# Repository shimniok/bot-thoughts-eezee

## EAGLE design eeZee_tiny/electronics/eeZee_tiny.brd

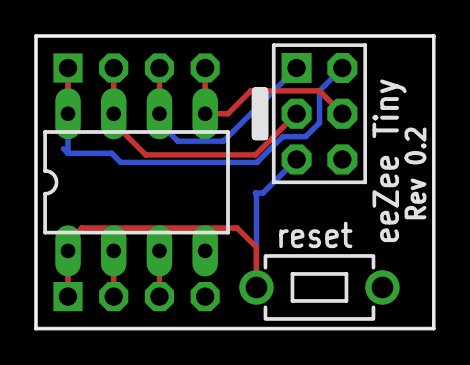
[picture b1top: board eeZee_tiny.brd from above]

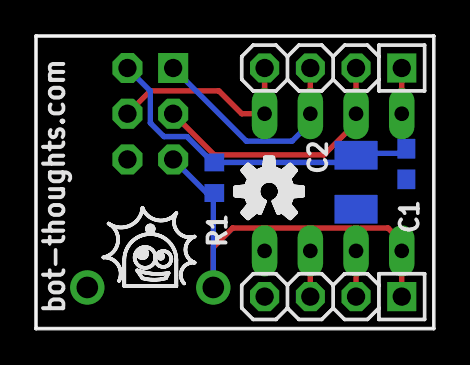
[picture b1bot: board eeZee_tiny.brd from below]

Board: 2 copper layers, 22.1 x 16.3 mm, 8 parts (5 on the bottom side), 8 nets.

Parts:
C1: 0.1uF; C0603
C2: 100uF; SMC_B
IC1: attiny; DIL08
J2: avrisp; CON6P2R
JP3, JP4: 1X04-S
R1: 10k; R0603
S1: reset; 6MMTACTILE_RECT

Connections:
!RESET: IC1.1, J2.5, JP3.1, R1.1, S1.P$1
GND: C1.2, C2.-, IC1.4, J2.6, JP3.4, S1.P$2
MISO: IC1.6, J2.1, JP4.3
MOSI: IC1.5, J2.4, JP4.4
unnamed: IC1.2, JP3.2
unnamed: IC1.3, JP3.3
SCK: IC1.7, J2.3, JP4.2
VCC: C1.1, C2.+, IC1.8, J2.2, JP4.1, R1.2

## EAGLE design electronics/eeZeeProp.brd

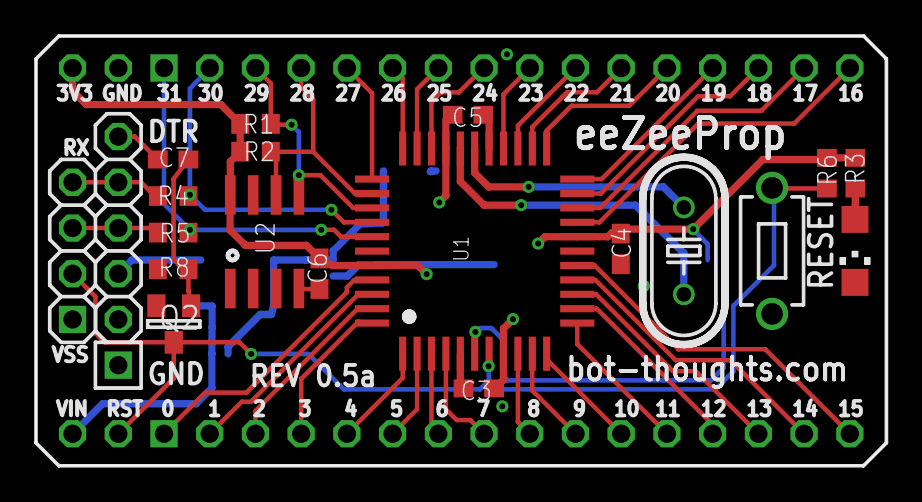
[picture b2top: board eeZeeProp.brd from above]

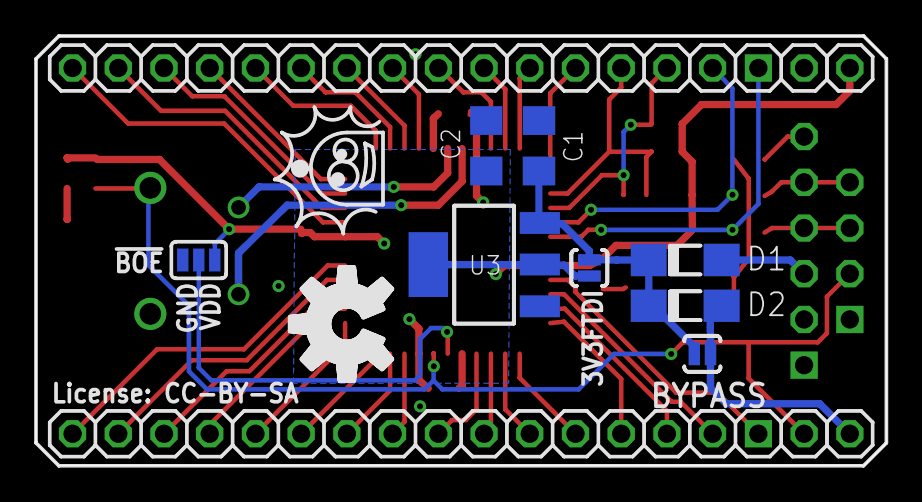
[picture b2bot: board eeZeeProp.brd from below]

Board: 2 copper layers, 47.2 x 23.9 mm, 34 parts (14 on the bottom side), 46 nets.

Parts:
C1, C2: 10uF; C1206
C3, C4, C5, C6, C7: 0.1uF; C0603
D1, D2: MBR130LSFT1; SOD123FL
JP1, JP5: 1X16-S
JP2: VIN; 1X01
JP3: PROP PLUG; 1X04-S
JP4: FTDI; 1X06-S
JP6: GND; 1X01
JP7: !RES; 1X01
JP8: 3V3; 1X01
LED1: green; CHIPLED_1206
Q1: 5MHz; HC49U-V
Q2: 2N3904SOT23; SOT-23
R1, R2, R4, R5, R8: 10k; R0603
R3: 330; R0603
R6: 1k; R0603
SJ1: BYPASS; SJ_2S-NO
SJ2: !BOE; SJ_3
SJ3: 3V3FTDI; SJ_2S-NO
SW1: RESET; 6MMTACTILE_RECT
U1: P8X32A-Q44
U2: 24LC256-I/ST; SO-08
U3: NCP1117 3V3; SOT223

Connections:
!BOE: SJ2.2, U1.6
!RES: JP3.2, JP7.1, Q2.1, R6.2, SW1.P$1, U1.7
DTR: C7.2, JP4.6
GND: C1.2, C2.2, C3.2, C4.2, C5.2, C6.2, JP3.1, JP4.1, JP6.1, LED1.C, Q2.2, R8.1, SJ2.1, SW1.P$2, U1.5, U1.17, U1.27, U1.39, U2.1, U2.2, U2.3, U2.4, U2.7, U3.1
unnamed: JP5.1, U1.41
unnamed: JP5.2, U1.42
unnamed: JP5.3, U1.43
unnamed: JP5.4, U1.44
unnamed: LED1.A, R3.1
unnamed: JP5.5, U1.1
unnamed: JP5.6, U1.2
unnamed: JP5.7, U1.3
unnamed: JP5.8, U1.4
unnamed: JP5.9, U1.9
unnamed: JP5.10, U1.10
unnamed: JP5.11, U1.11
unnamed: JP5.12, U1.12
unnamed: JP5.13, U1.13
unnamed: JP5.14, U1.14
unnamed: JP5.15, U1.15
unnamed: JP5.16, U1.16
unnamed: JP1.5, U1.34
unnamed: JP1.6, U1.33
unnamed: JP1.7, U1.32
unnamed: JP1.8, U1.31
unnamed: JP1.9, U1.26
unnamed: JP1.10, U1.25
unnamed: JP1.11, U1.24
unnamed: JP1.12, U1.23
unnamed: JP1.13, U1.22
unnamed: JP1.14, U1.21
unnamed: JP1.15, U1.20
unnamed: JP1.16, U1.19
unnamed: C7.1, Q2.3, R8.2
P28: JP1.4, R2.1, U1.35, U2.6
P29: JP1.3, R1.1, U1.36, U2.5
P30: JP1.2, R4.2, U1.37
P31: JP1.1, R5.2, U1.38
RXI: JP3.4, JP4.5, R4.1
TXO: JP3.3, JP4.4, R5.1
V+: C1.1, D1.C, D2.C, SJ1.2, SJ3.2, U3.3
VDD: C2.1, C3.1, C4.1, C5.1, C6.1, JP8.1, R1.2, R2.2, R3.2, R6.1, SJ2.3, SJ3.1, U1.8, U1.18, U1.30, U1.40, U2.8, U3.2, U3.4
VIN: D2.A, JP2.1, SJ1.1
VUSB: D1.A, JP4.3
XI: Q1.2, U1.28
XO: Q1.1, U1.29

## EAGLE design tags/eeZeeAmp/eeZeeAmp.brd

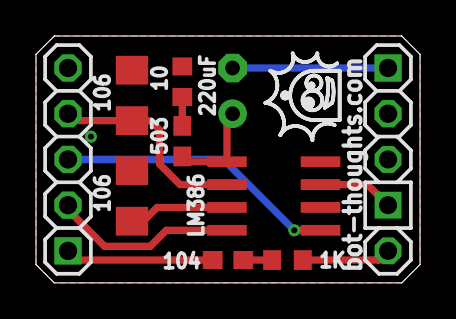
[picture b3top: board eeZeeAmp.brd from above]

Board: 2 copper layers, 21.3 x 13.7 mm, 11 parts (1 on the bottom side), 12 nets.

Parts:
C1: 220uF; E2,5-6
C2: 104; C0603
C3: 503; C0603
C4, C5: 106; C1206
IC1: LM386; SO08
JP1: 1X05-S
JP2: SPKR; 1X02-S
R1: 10; R0603
R2: VOL; OFFBOARD_POT_3
R3: 1K; R0603

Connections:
AUDIO: C2.1, JP1.1
G1: IC1.1, JP1.3
G8: IC1.8, JP1.2
GND: C4.2, C5.2, IC1.2, IC1.4, JP1.5, JP2.2, R1.1, R2.P$1
unnamed: IC1.3, R2.P$2
unnamed: C2.2, R3.2
unnamed: C1.+, C3.1, IC1.5
unnamed: C3.2, R1.2
unnamed: C5.1, IC1.7
unnamed: R2.P$3, R3.1
SP+: C1.-, JP2.1
VCC: C4.1, IC1.6, JP1.4

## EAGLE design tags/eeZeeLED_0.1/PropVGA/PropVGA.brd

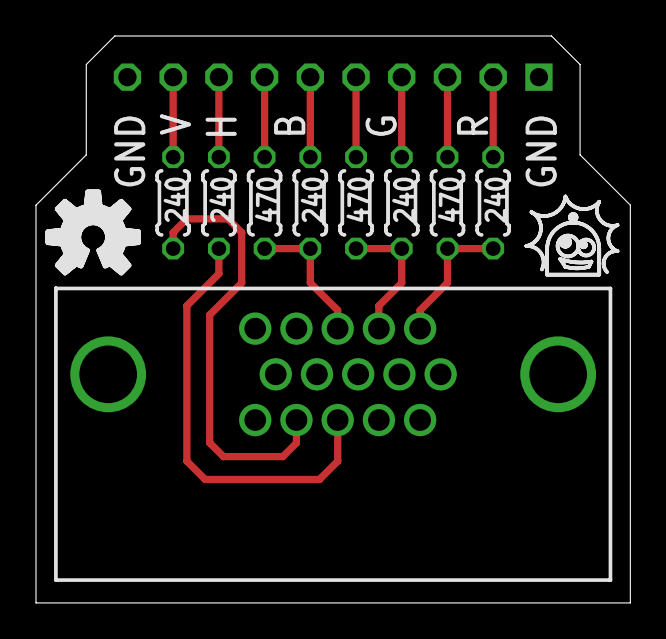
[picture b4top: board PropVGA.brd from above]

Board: 2 copper layers, 33.0 x 31.5 mm, 10 parts (1 on the bottom side), 14 nets.

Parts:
JP2: VGA; FCI_DSUB_HD_15_RA
JP3: 1X10-S
R1, R2, R4, R6, R8: 240; 0204/5
R3, R5, R7: 470; 0204/5

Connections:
B: JP2.P3, R3.1, R4.1
G: JP2.P2, R5.1, R6.1
GND: JP2.P5, JP2.P6, JP2.P7, JP2.P8, JP2.P9, JP2.P10, JP3.1, JP3.10
H: JP2.P13, R2.1
unnamed: JP3.9, R1.2
unnamed: JP3.8, R2.2
unnamed: JP3.7, R3.2
unnamed: JP3.6, R4.2
unnamed: JP3.5, R5.2
unnamed: JP3.4, R6.2
unnamed: JP3.3, R7.2
unnamed: JP3.2, R8.2
R: JP2.P1, R7.1, R8.1
V: JP2.P14, R1.1

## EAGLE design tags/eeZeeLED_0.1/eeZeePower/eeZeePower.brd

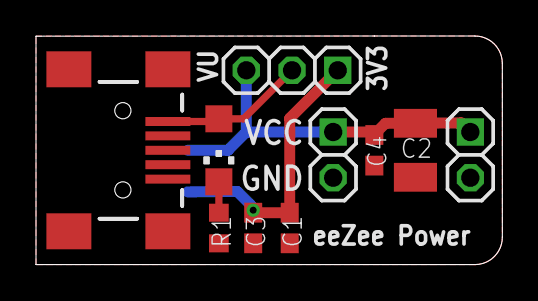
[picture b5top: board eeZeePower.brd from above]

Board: 2 copper layers, 25.9 x 12.7 mm, 11 parts (1 on the bottom side), 5 nets.

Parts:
C1, C4: 0.1uF; C0603
C2: 100uF; SMC_B
C3: 10uF; C0603
JP1: USBSMD; USB-MINIB
JP3, JP4: 1X02-S
JP10: SEL; 1X03-S
LED1: CHIPLED_1206
R1: R0603
U1: SOT223

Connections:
GND: C1.2, C2.-, C3.2, C4.2, JP1.GND, JP3.2, JP4.2, R1.1, U1.1
unnamed: LED1.C, R1.2
VBUS: JP1.VBUS, JP10.2, LED1.A
VIN: C1.1, C3.1, JP10.1, U1.3
VOUT: C2.+, C4.1, JP3.1, JP4.1, JP10.3, U1.2

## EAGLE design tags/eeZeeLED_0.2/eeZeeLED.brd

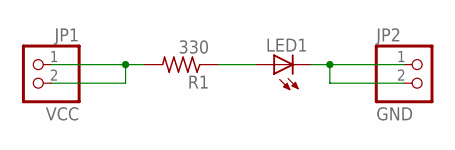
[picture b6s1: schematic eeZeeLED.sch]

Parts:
JP1: VCC; 1X02-S
JP2: GND; 1X02-S
LED1: LEDCHIPLED_1206; CHIPLED_1206
R1: 330; R0603

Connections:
unnamed: LED1.A, R1.1
unnamed: JP2.1, JP2.2, LED1.C
unnamed: JP1.1, JP1.2, R1.2

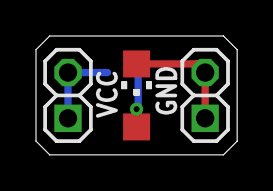
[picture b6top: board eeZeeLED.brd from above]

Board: 2 copper layers, 11.2 x 6.6 mm, 4 parts (1 on the bottom side), 3 nets.

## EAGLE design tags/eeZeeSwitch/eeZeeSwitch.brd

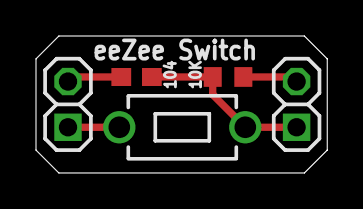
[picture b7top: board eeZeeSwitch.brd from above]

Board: 2 copper layers, 16.2 x 7.6 mm, 5 parts (0 on the bottom side), 4 nets.

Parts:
C1: 104; C0603
JP1, JP2: 1X02-S
R1: 10K; R0603
S1: eeZee Switch; 6MMTACTILE_RECT

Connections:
DEBOUNCE: C1.2, JP2.2
PULLUP: JP1.2, R1.2
S1A: JP2.1, S1.P$1
S1B: C1.1, JP1.1, R1.1, S1.P$2

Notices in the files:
electronics/eeZeeProp.brd:
License: CC-BY-SA
parts and their libraries:
SparkFun: Licensing: CC v3.0 Share-Alike You are welcome to use this library for commercial purposes.
